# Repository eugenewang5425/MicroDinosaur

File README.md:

# MicroDinosaur

基于 Microduck 改型的小型双足恐龙机器人，使用 S288 舵机、Radxa ZERO 3W、Blender 和 Python。当前工作包括机械与打印适配、板载深度感知、IMU 接入和双总线电控设计。开发中使用 AI 辅助；来源与许可见 [NOTICE](NOTICE.md)。

**更新至 2026-11-08。默认分支只保存最新交付文件，旧版本可从 Git 提交历史查看。** 当前仍为研究原型，实机站立、行走、完整装配和制造验证尚未完成。

| 内容 | 当前入口 | 状态 |
| --- | --- | --- |
| 整机 CAD | [MicroDinosaur_Current.blend](current/MicroDinosaur_Current.blend) | OS-M02，11 月 2 日更新；150 对象、124 网格、6 条保留驱动 |
| 打印工程 | [MicroDinosaur_Print.3mf](current/MicroDinosaur_Print.3mf) | 8 盘 30 件，与当前模型配套 |
| 整机零位校准架 | [三件夹具、两盘工程与示意图](current/calibration_fixture/README.md) | 11月8日最新试装版；两盘切片通过，实物配合与承载待验 |
| 头部集成板 | [KiCad 工程与说明](hardware/head_hat/README.md) | 65×30 mm 六层；原生 DRC 0 错误、0 警告、0 未连接；未打样验收 |
| S288 主机接口 | [双总线适配代码](hardware/head_hat/software/README.md) | 帧编码、CRC、端口绑定与 EEPROM 工具；待实板联调 |
| IMU | [接线、读取程序与数据](hardware/imu/README.md) | F411 与 ZERO 3W 基础读取通过；异常跳点待排查 |
| 板载感知 | [当前源码、模型与复测边界](software/perception/README.md) | 相机/NPU 功能已恢复；散热后持续性能待复测 |

完整阶段和下一步见 [项目状态](PROJECT_STATUS.md)，机械使用边界见 [当前设计](CURRENT_DESIGN.md)。

## 获取与检查

```sh
git lfs install
git clone https://github.com/eugenewang5425/MicroDinosaur.git
cd MicroDinosaur
git lfs pull
python scripts/verify_current.py
```

CAD 和 RKNN 权重通过 Git LFS 保存。直接下载 ZIP 时，需确认大文件不是 LFS 指针。用 Blender 4.5 打开 `current/MicroDinosaur_Current.blend`，用 Bambu Studio 打开原生 `current/MicroDinosaur_Print.3mf`；先核对打印机、材料和工艺。读取或打开文件不会下发打印任务。

当前模型保留 19 个舵机参照实例，但只有 6 条现有驱动；不能据此宣称完整 19 轴运动链已经绑定。旧 v07 的质量台账、19 驱动和仿真验收不适用于当前 OS-M02。

仓库不保存中间整机、`.blend1`、前后重复副本、过程截图、失败候选、完整日志、工具安装包、个人设备配置和实时标定记录。各模块只附与本次交付有关的最终检查或测量结果。

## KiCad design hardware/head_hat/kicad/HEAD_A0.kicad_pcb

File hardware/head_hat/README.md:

# 当前头部集成板

最新候选：**B2 V3 / 2026-11-07**。65×30 mm，六层，279 个过孔、3938 段走线。KiCad 9.0.9 原生 DRC 为 0 错误、0 警告、0 未连接。当前为设计审阅候选，尚未实物打样与制造放行。

打开 [kicad/HEAD_A0.kicad_pro](kicad/HEAD_A0.kicad_pro)。工程内部文件名沿用 HEAD_A0，不代表这是早期 A0 版本；本目录只包含这一份最新候选。符号与封装库使用 `${KIPRJMOD}` 相对引用，已随工程保存。[BOM](BOM.csv) 对应保留的 B2 器件布置。

功能包括降压与电源保护、音频、板载头部 IMU、FT2232H 双 UART 与两路 S288 半双工接口，并保留身体 IMU、ToF 接口。独立串口与协议适配代码见 [software](software/README.md)。FT2232H 自带 USB/UART，不需要烧写宇树 STM32 示例。

最终 [DRC](validation/final_drc.json) 与 [几何汇总](validation/summary.json) 绑定 PCB SHA256 `566901eef7e306b5e4f0bd7f48aab18467615563099a4b934d516693c2ad7f8a`。115 个接地过孔与 71 个供电过孔保留；USB 差分对和有源 MEMS 时钟铜线保留。检测到的同层共线重复段为 0；这是局部 CAD 检查结果，不是信号完整性或实物性能结论。

本版未完成实板时钟、USB 阻抗、EMI、最大电流/温升或整机装配验证。Radxa 的 USB GPIO 引出需要核对并执行相应硬件电阻选择，当前不是即插即用连接。S288 整串动力仍需电池分组注电，PH 接口和支路保险不等于整腿堵转电流承载能力。本包不提供旧 B2 的 Gerber，避免与当前走线混用；投板前须以本版原生工程完成电气与制造复核。

来源与许可见 [NOTICE](NOTICE.md) 和 [LICENSE](LICENSE)。

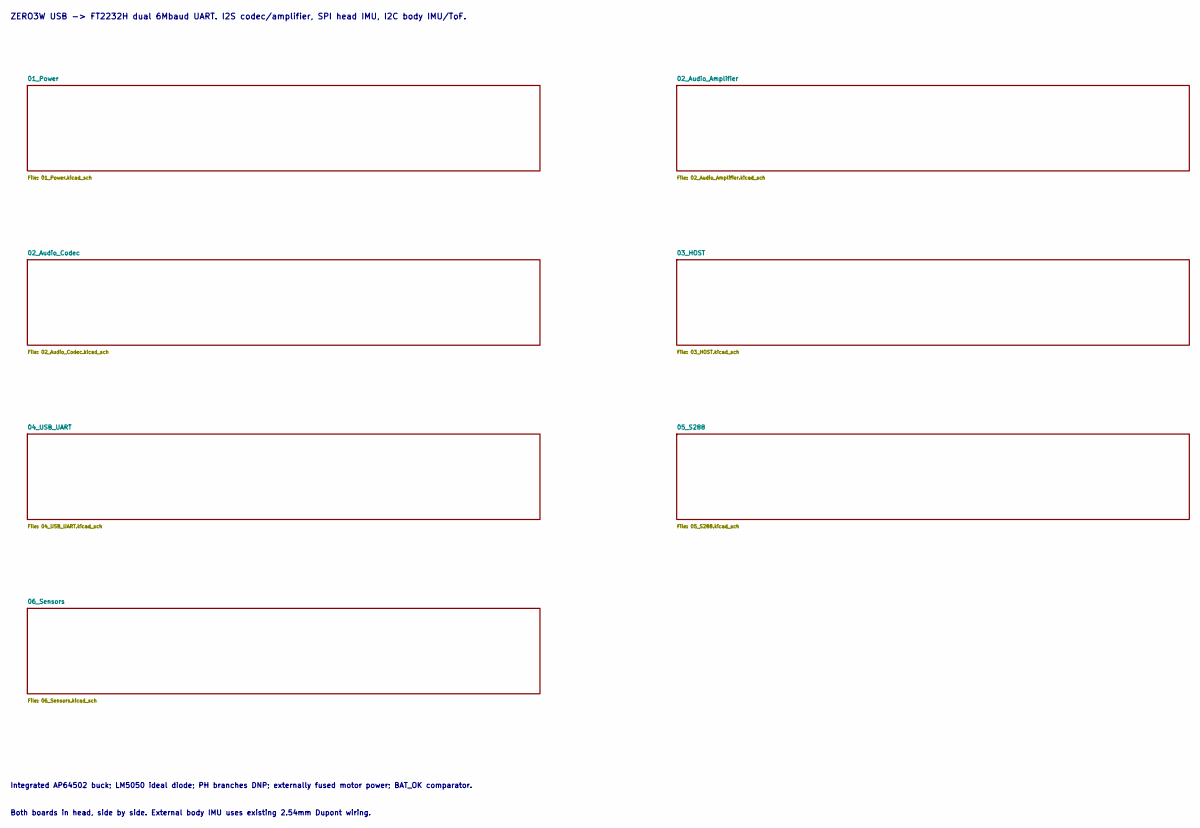
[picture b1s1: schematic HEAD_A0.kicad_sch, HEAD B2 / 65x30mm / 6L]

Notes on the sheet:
ZERO3W USB -> FT2232H dual 6Mbaud UART. I2S codec/amplifier, SPI head IMU, I2C body IMU/ToF.
Integrated AP64502 buck; LM5050 ideal diode; PH branches DNP; externally fused motor power; BAT_OK comparator.
Both boards in head, side by side. External body IMU uses existing 2.54mm Dupont wiring.

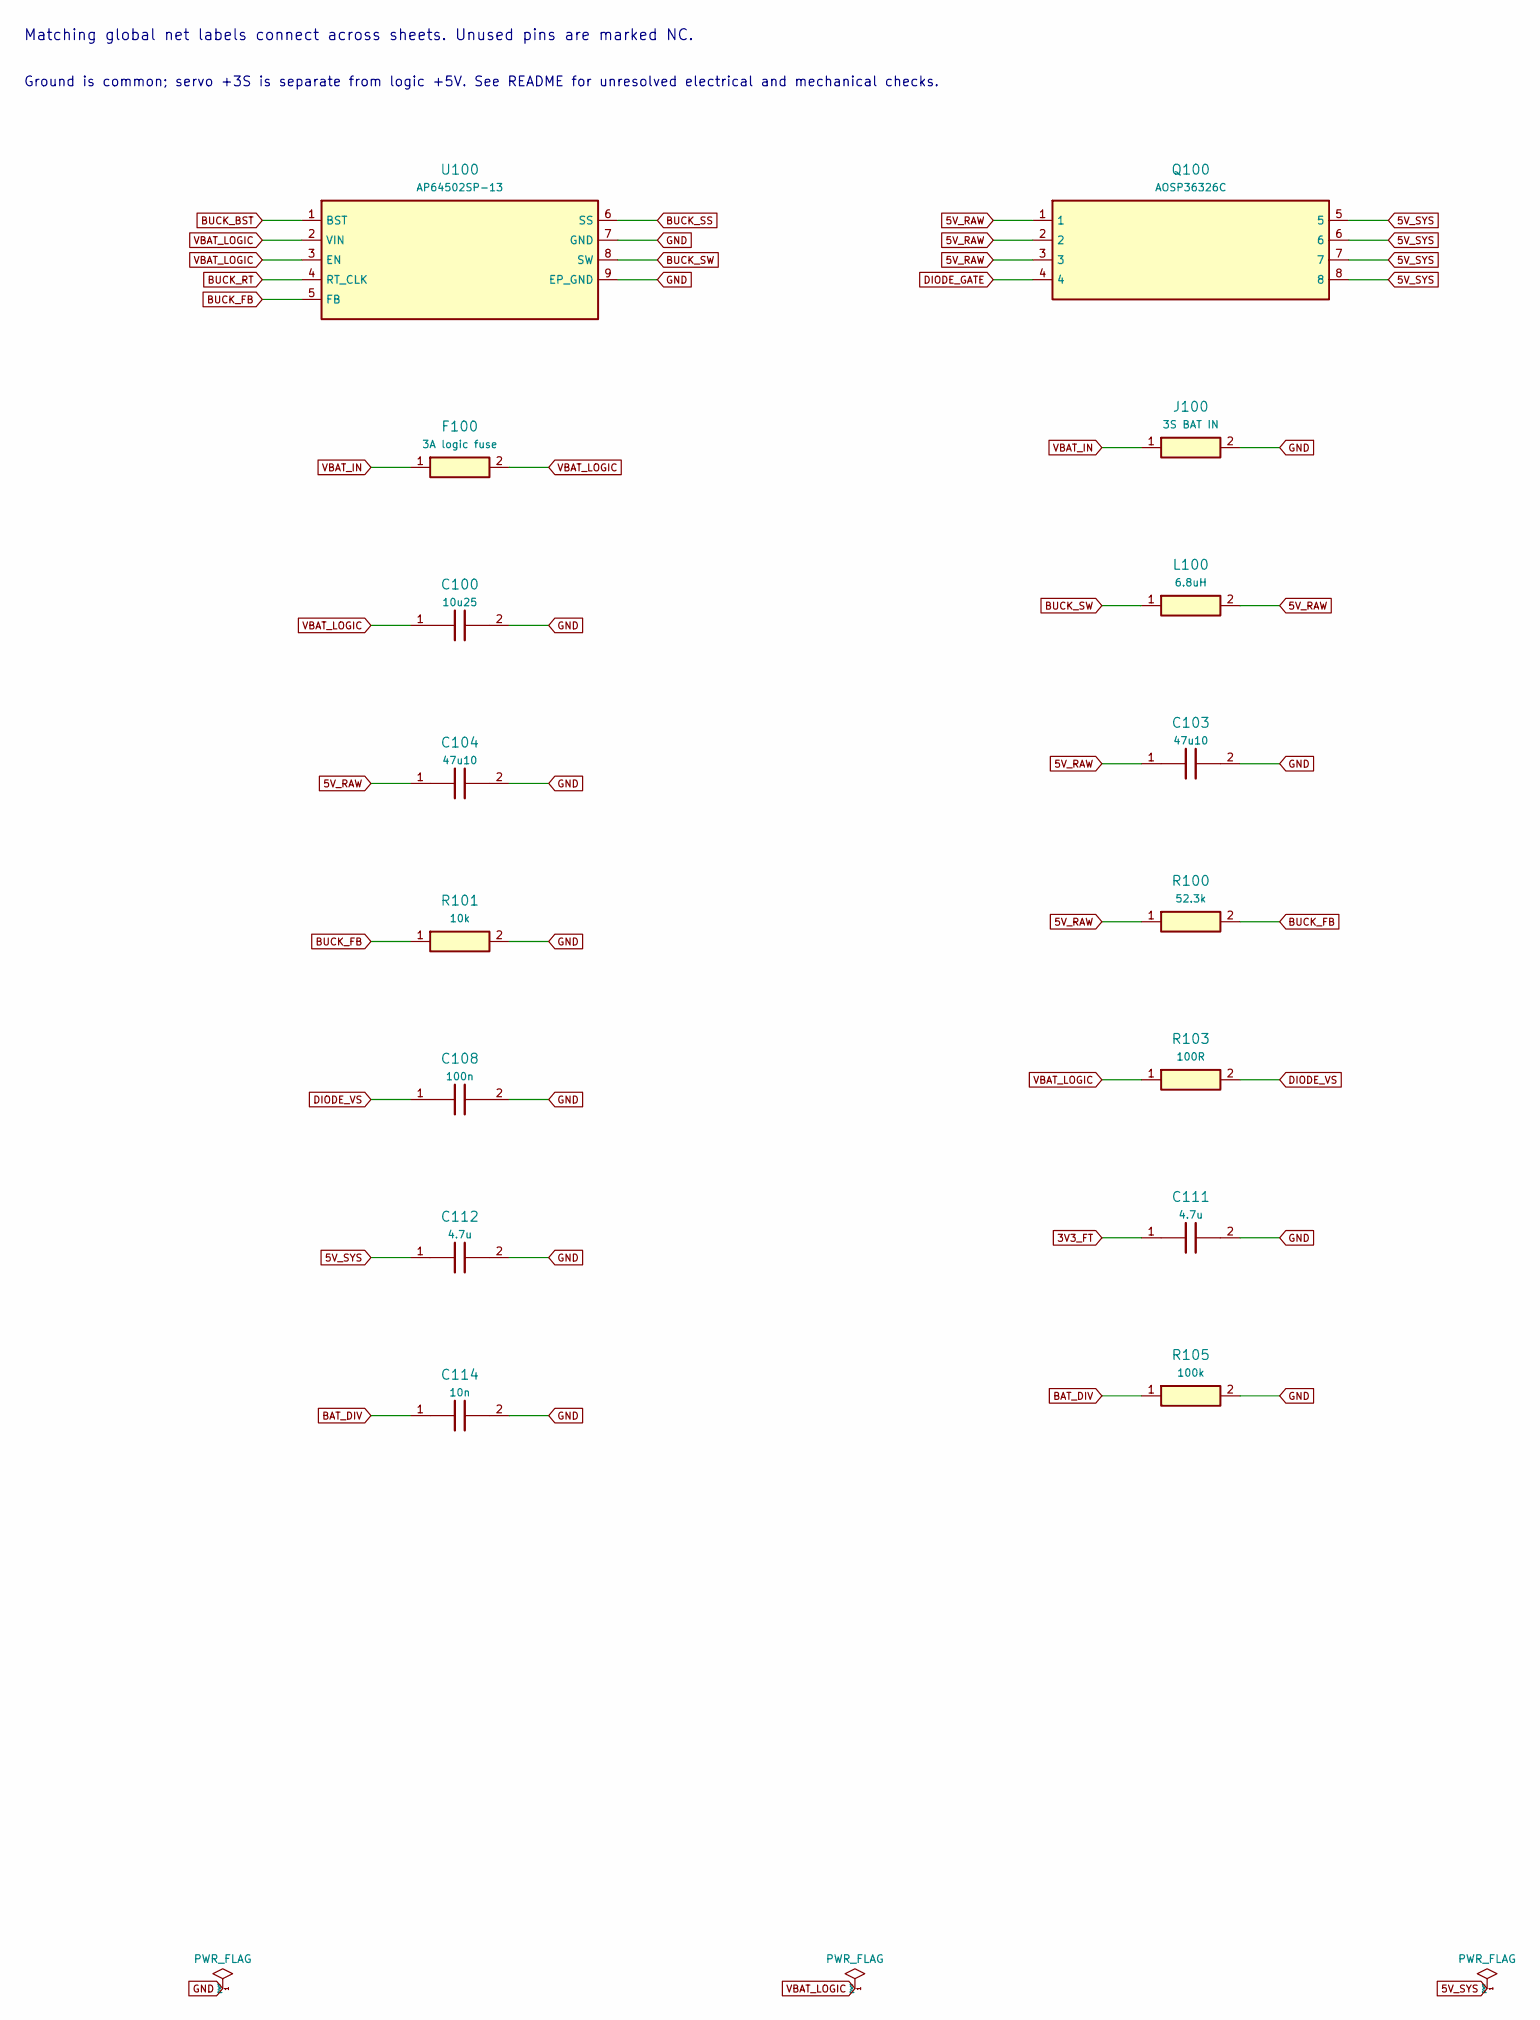
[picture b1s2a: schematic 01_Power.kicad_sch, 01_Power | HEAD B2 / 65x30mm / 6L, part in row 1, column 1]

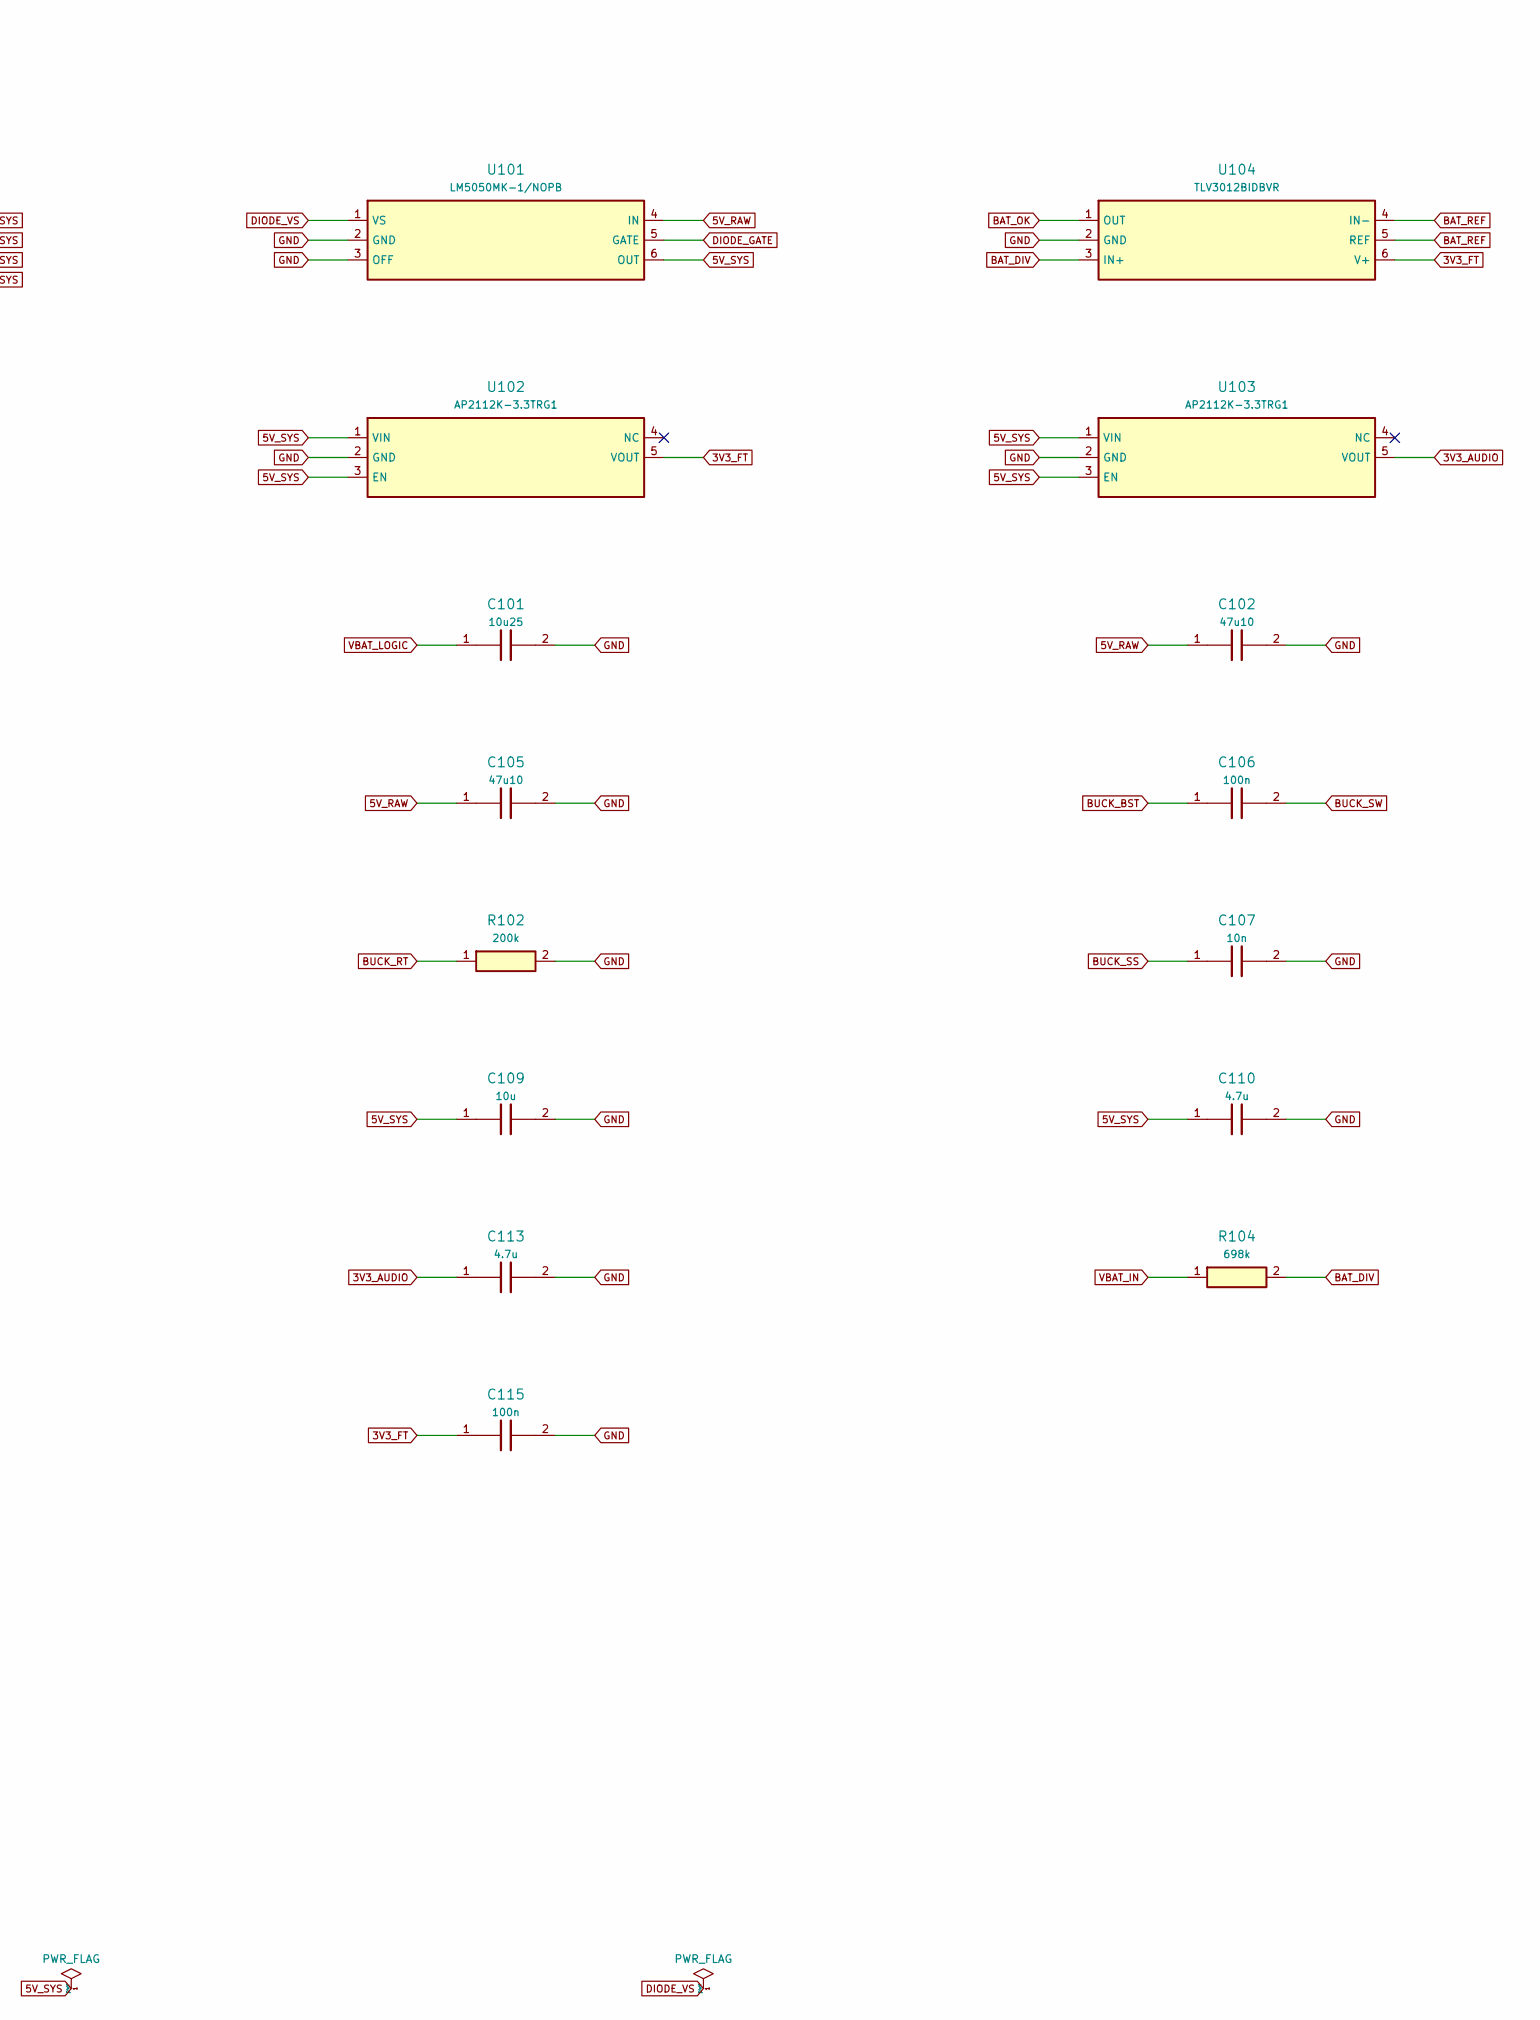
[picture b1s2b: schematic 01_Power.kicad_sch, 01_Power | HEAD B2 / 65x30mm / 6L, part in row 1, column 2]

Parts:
C100, C101: 10u25; Capacitor_SMD__C_1206_3216Metric; MPN GRM31CR71E106KA12L
C102, C103, C104, C105: 47u10; Capacitor_SMD__C_1210_3225Metric; MPN GRM32ER71A476KE15L
C106, C115: 100n; Capacitor_SMD__C_0402_1005Metric; MPN GRM155R71C104KA88D
C107, C114: 10n; Capacitor_SMD__C_0402_1005Metric; MPN GRM155R71H103KA88D
C108: 100n; Capacitor_SMD__C_0402_1005Metric; MPN GRM155R71H104KE14D
C109: 10u; Capacitor_SMD__C_0603_1608Metric; MPN GRM188R61A106KE69D
C110, C111, C112, C113: 4.7u; Capacitor_SMD__C_0603_1608Metric; MPN GRM188R60J475KE19D
F100: 3A logic fuse; Fuse__Fuse_1206_3216Metric; MPN 0467003.NR
J100: 3S BAT IN; Connector_Molex__Molex_Nano-Fit_105313-xx02_1x02_P2.50mm_Ho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; MPN 1053131202
L100: 6.8uH; Inductor_SMD__L_Coilcraft_XAL6060-XXX; MPN XAL6060-682MEC
Q100: AOSP36326C; Package_SO__SOIC-8_3.9x4.9mm_P1.27mm; MPN AOSP36326C
R100: 52.3k; Resistor_SMD__R_0402_1005Metric; MPN RC0402FR-0752K3L
R101: 10k; Resistor_SMD__R_0402_1005Metric; MPN RC0402FR-0710KL
R102: 200k; Resistor_SMD__R_0402_1005Metric; MPN RC0402FR-07200KL
R103: 100R; Resistor_SMD__R_0402_1005Metric; MPN RC0402FR-07100RL
R104: 698k; Resistor_SMD__R_0402_1005Metric; MPN RC0402FR-07698KL
R105: 100k; Resistor_SMD__R_0402_1005Metric; MPN RC0402FR-07100KL
U100: AP64502SP-13; AP64502_SO8EP; MPN AP64502SP-13
U101: LM5050MK-1/NOPB; Package_TO_SOT_SMD__SOT-23-6; MPN LM5050MK-1/NOPB
U102, U103: AP2112K-3.3TRG1; Package_TO_SOT_SMD__SOT-23-5; MPN AP2112K-3.3TRG1
U104: TLV3012BIDBVR; Package_TO_SOT_SMD__SOT-23-6; MPN TLV3012BIDBVR

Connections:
3V3_AUDIO: C113.1, U103.5 (VOUT); also elsewhere on the board
3V3_FT: C111.1, C115.1, U102.5 (VOUT), U104.6 (V+); also elsewhere on the board
5V_RAW: C102.1, C103.1, C104.1, C105.1, L100.2, Q100.1, Q100.2, Q100.3, R100.1, U101.4 (IN)
5V_SYS: C109.1, C110.1, C112.1, Q100.5, Q100.6, Q100.7, Q100.8, U101.6 (OUT), U102.1 (VIN), U102.3 (EN), U103.1 (VIN), U103.3 (EN); also elsewhere on the board
BAT_DIV: C114.1, R104.2, R105.1, U104.3 (IN+)
BAT_OK: U104.1 (OUT); also elsewhere on the board
BAT_REF: U104.4 (IN-), U104.5 (REF)
BUCK_BST: C106.1, U100.1 (BST)
BUCK_FB: R100.2, R101.1, U100.5 (FB)
BUCK_RT: R102.1, U100.4 (RT_CLK)
BUCK_SS: C107.1, U100.6 (SS)
BUCK_SW: C106.2, L100.1, U100.8 (SW)
DIODE_GATE: Q100.4, U101.5 (GATE)
DIODE_VS: C108.1, R103.2, U101.1 (VS)
GND: C100.2, C101.2, C102.2, C103.2, C104.2, C105.2, C107.2, C108.2, C109.2, C110.2, C111.2, C112.2, C113.2, C114.2, C115.2, J100.2, R101.2, R102.2, R105.2, U100.7 (GND), U100.9 (EP_GND), U101.2 (GND), U101.3 (OFF), U102.2 (GND), U103.2 (GND), U104.2 (GND); also elsewhere on the board
VBAT_IN: F100.1, J100.1, R104.1; also elsewhere on the board
VBAT_LOGIC: C100.1, C101.1, F100.2, R103.1, U100.2 (VIN), U100.3 (EN)

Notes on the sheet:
Matching global net labels connect across sheets. Unused pins are marked NC.
Ground is common; servo +3S is separate from logic +5V. See README for unresolved electrical and mechanical checks.

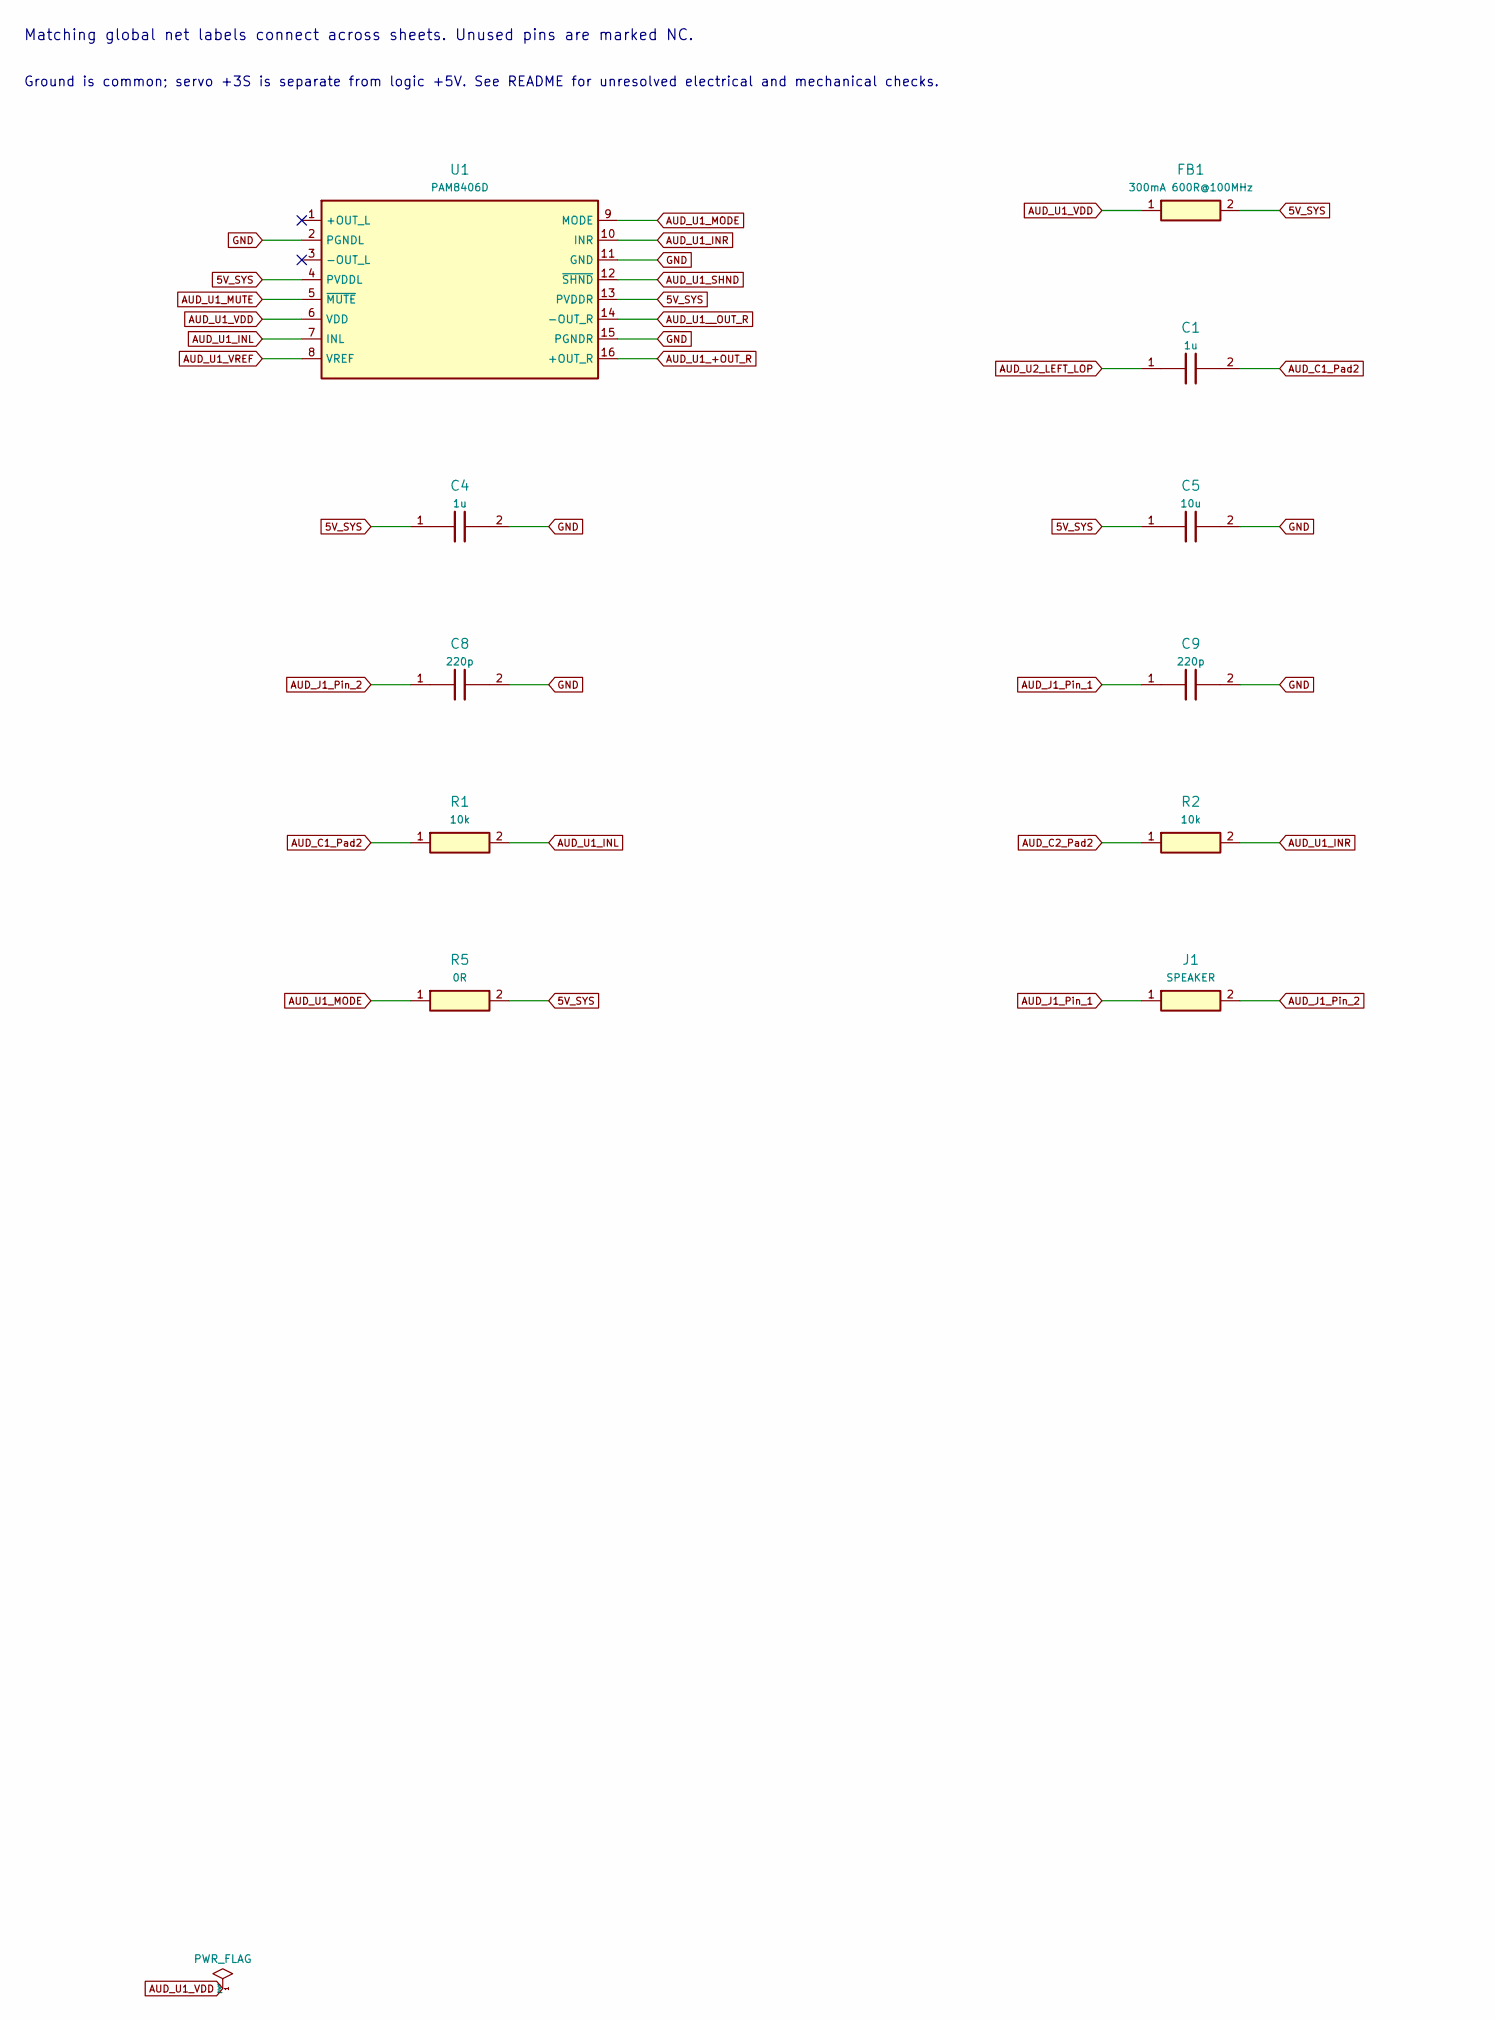
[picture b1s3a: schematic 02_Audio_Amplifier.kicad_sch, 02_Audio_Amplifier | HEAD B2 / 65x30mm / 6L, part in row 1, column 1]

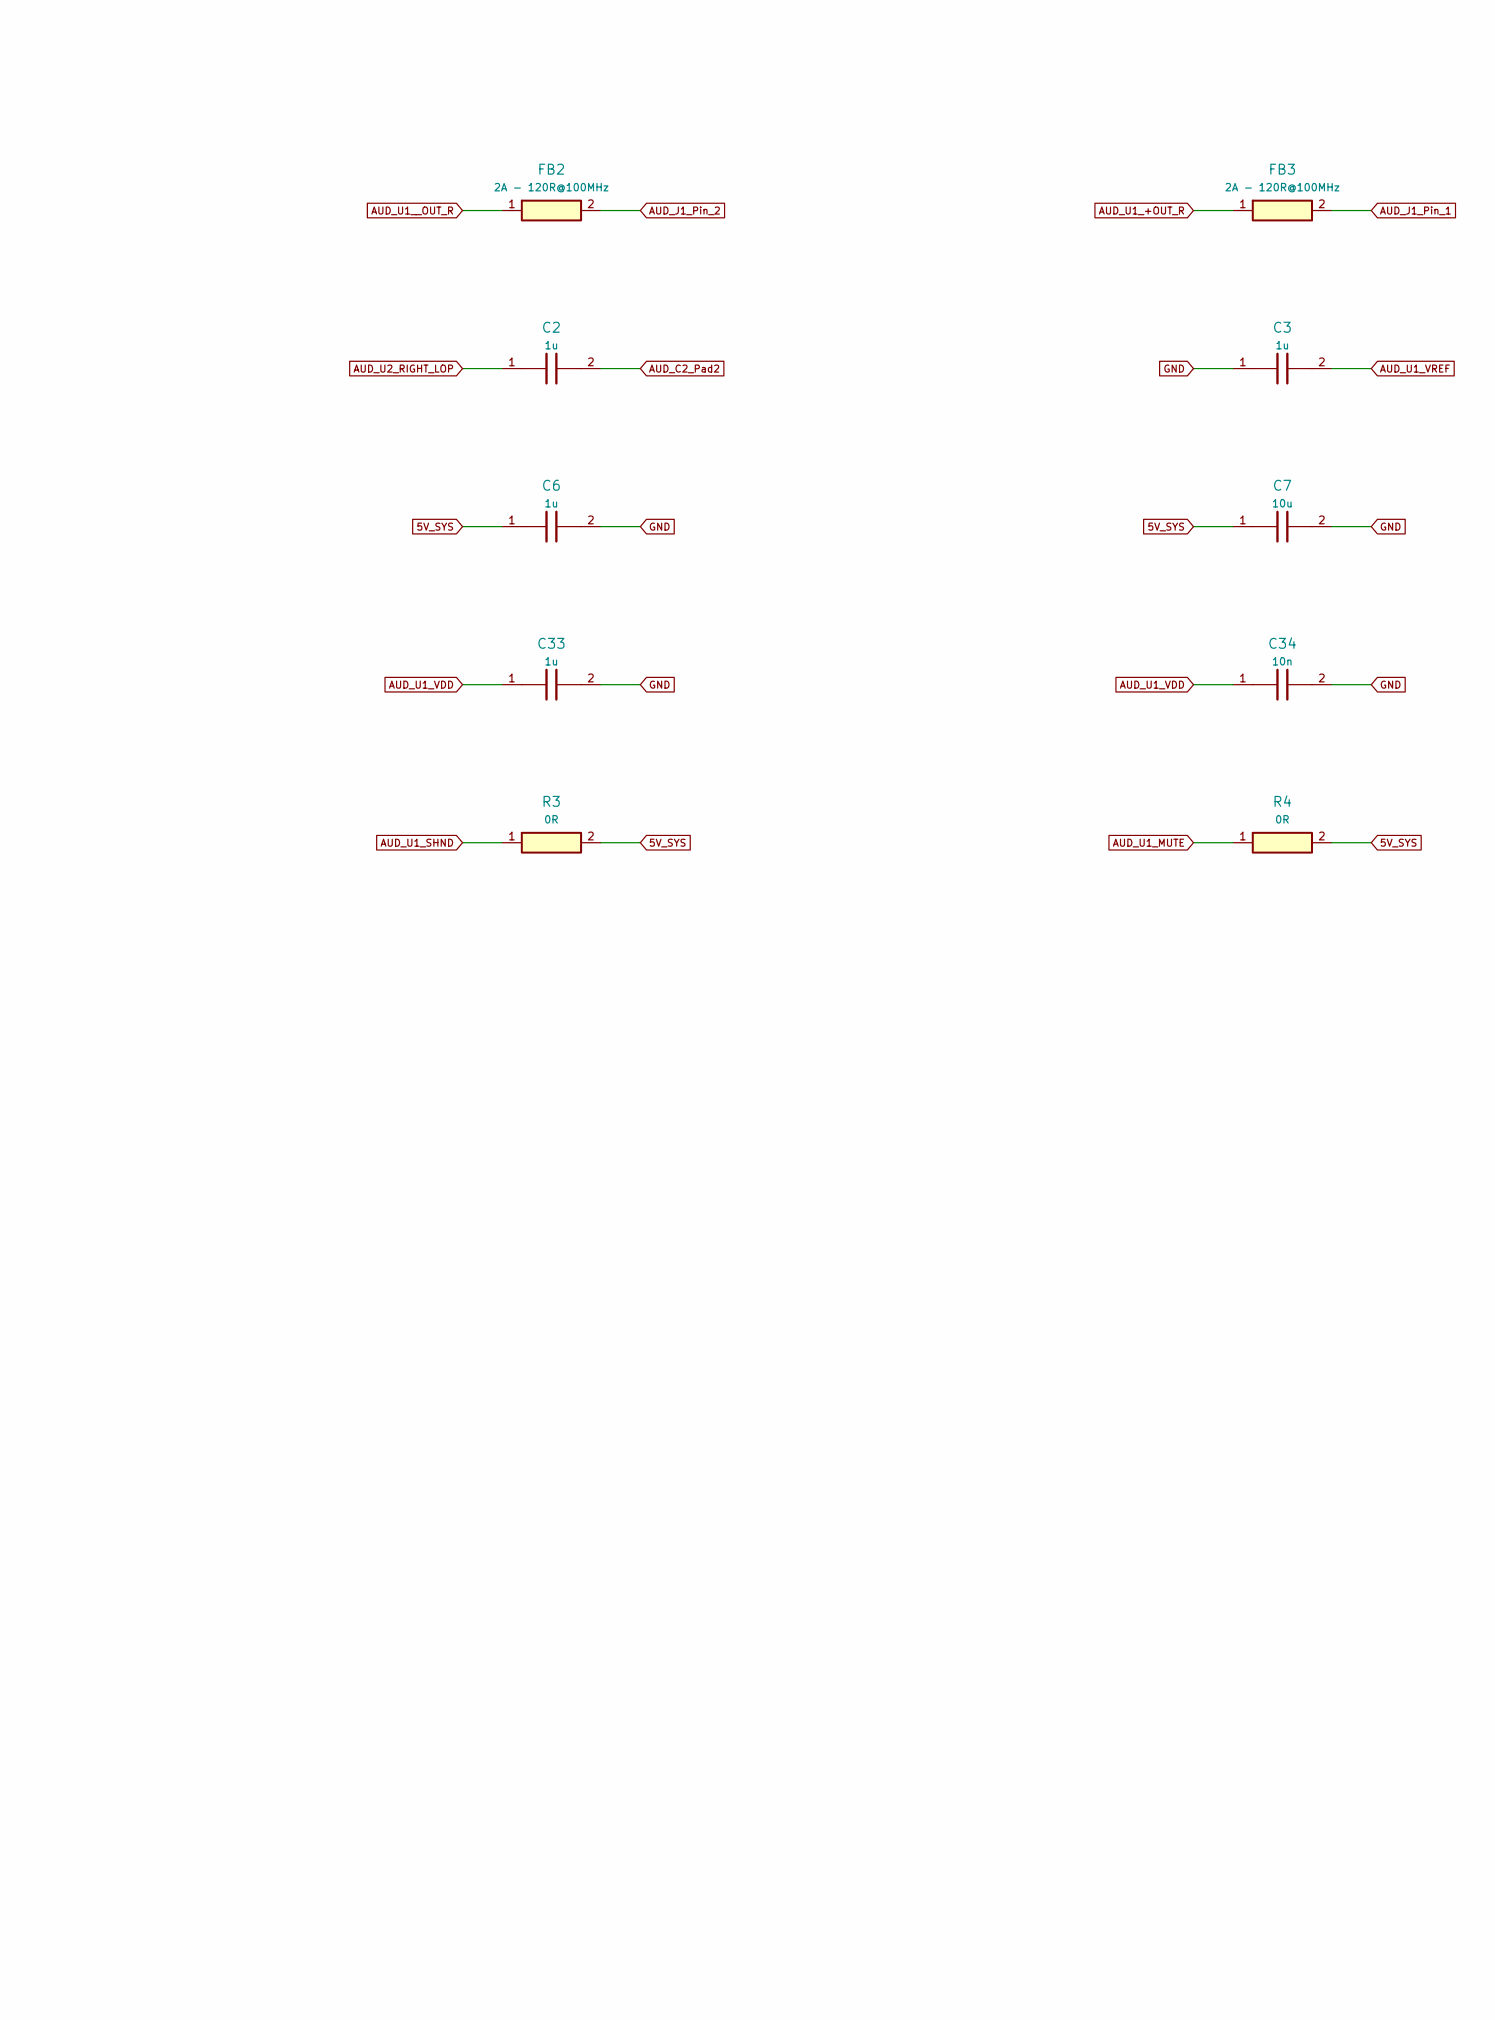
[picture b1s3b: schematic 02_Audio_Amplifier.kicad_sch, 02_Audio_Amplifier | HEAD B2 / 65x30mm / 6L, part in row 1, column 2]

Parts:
C1, C2, C3, C4, C6, C33: 1u; Capacitor_SMD__C_0402_1005Metric; MPN GRM155R61A105KE15D
C5, C7: 10u; Capacitor_SMD__C_0603_1608Metric; MPN GRM188R61A106KE69D
C8, C9: 220p; Capacitor_SMD__C_0603_1608Metric; MPN GRM1885C1H221JA01D
C34: 10n; Capacitor_SMD__C_0402_1005Metric; MPN GRM155R71H103KA88D
FB1: 300mA 600R@100MHz; Pollen_FB1; MPN BLM15AG601SN1D
FB2: 2A - 120R@100MHz; Pollen_FB2; MPN BLM15PX121SN1D
FB3: 2A - 120R@100MHz; Pollen_FB3; MPN BLM15PX121SN1D
J1: SPEAKER; Connector_JST__JST_PH_B2B-PH-K_1x02_P2.00mm_Vertical; MPN B2B-PH-K-S
R1, R2: 10k; Resistor_SMD__R_0402_1005Metric; MPN RC0402FR-0710KL
R3, R4, R5: 0R; Resistor_SMD__R_0402_1005Metric; MPN RC0402JR-070RL
U1: PAM8406D; Pollen_U1; MPN PAM8406DR

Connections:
5V_SYS: C4.1, C5.1, C6.1, C7.1, FB1.2, R3.2, R4.2, R5.2, U1.4 (PVDDL), U1.13 (PVDDR); also elsewhere on the board
AUD_C1_Pad2: C1.2, R1.1
AUD_C2_Pad2: C2.2, R2.1
AUD_J1_Pin_1: C9.1, FB3.2, J1.1
AUD_J1_Pin_2: C8.1, FB2.2, J1.2
AUD_U1_+OUT_R: FB3.1, U1.16 (+OUT_R)
AUD_U1_INL: R1.2, U1.7 (INL)
AUD_U1_INR: R2.2, U1.10 (INR)
AUD_U1_MODE: R5.1, U1.9 (MODE)
AUD_U1_MUTE: R4.1, U1.5 (~MUTE)
AUD_U1_SHND: R3.1, U1.12 (~SHND)
AUD_U1_VDD: C33.1, C34.1, FB1.1, U1.6 (VDD)
AUD_U1_VREF: C3.2, U1.8 (VREF)
AUD_U1__OUT_R: FB2.1, U1.14 (-OUT_R)
AUD_U2_LEFT_LOP: C1.1; also elsewhere on the board
AUD_U2_RIGHT_LOP: C2.1; also elsewhere on the board
GND: C3.1, C4.2, C5.2, C6.2, C7.2, C8.2, C9.2, C33.2, C34.2, U1.2 (PGNDL), U1.11 (GND), U1.15 (PGNDR); also elsewhere on the board

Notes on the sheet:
Matching global net labels connect across sheets. Unused pins are marked NC.
Ground is common; servo +3S is separate from logic +5V. See README for unresolved electrical and mechanical checks.

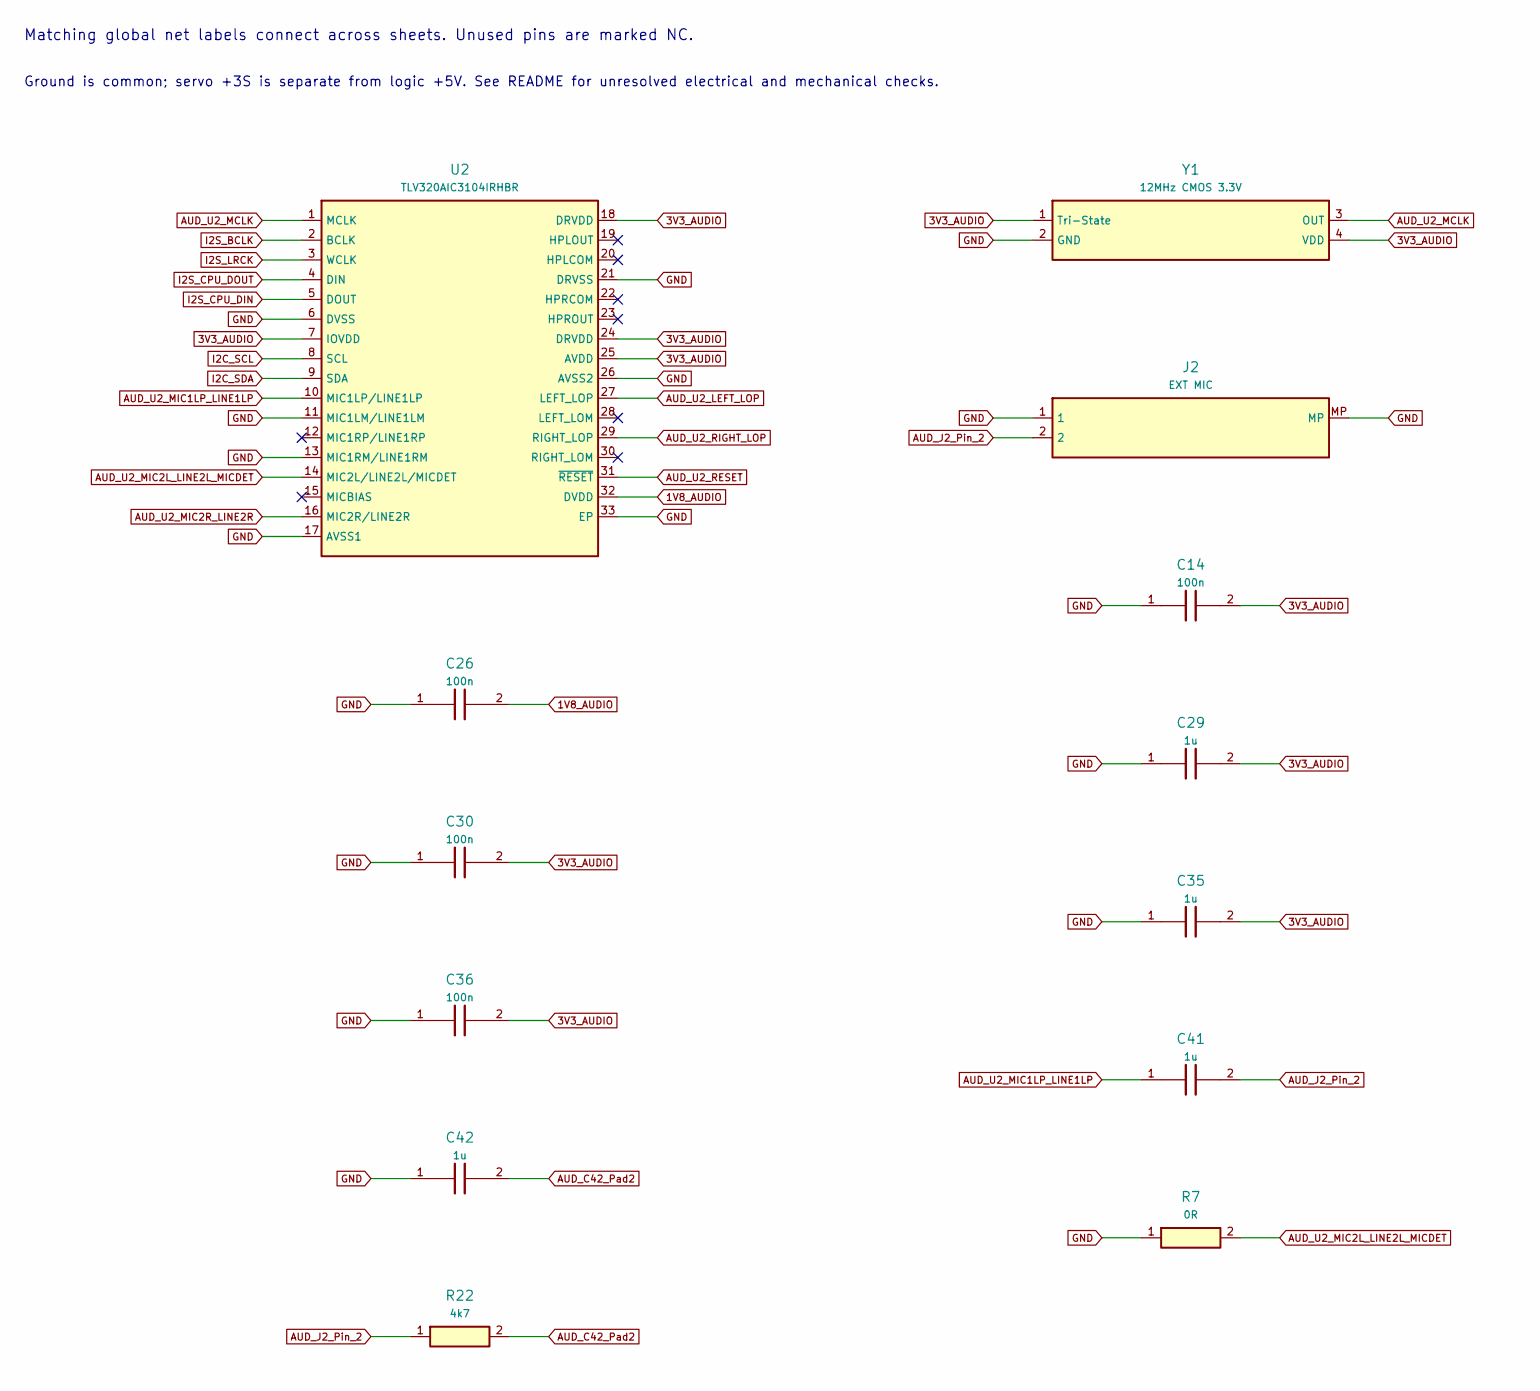
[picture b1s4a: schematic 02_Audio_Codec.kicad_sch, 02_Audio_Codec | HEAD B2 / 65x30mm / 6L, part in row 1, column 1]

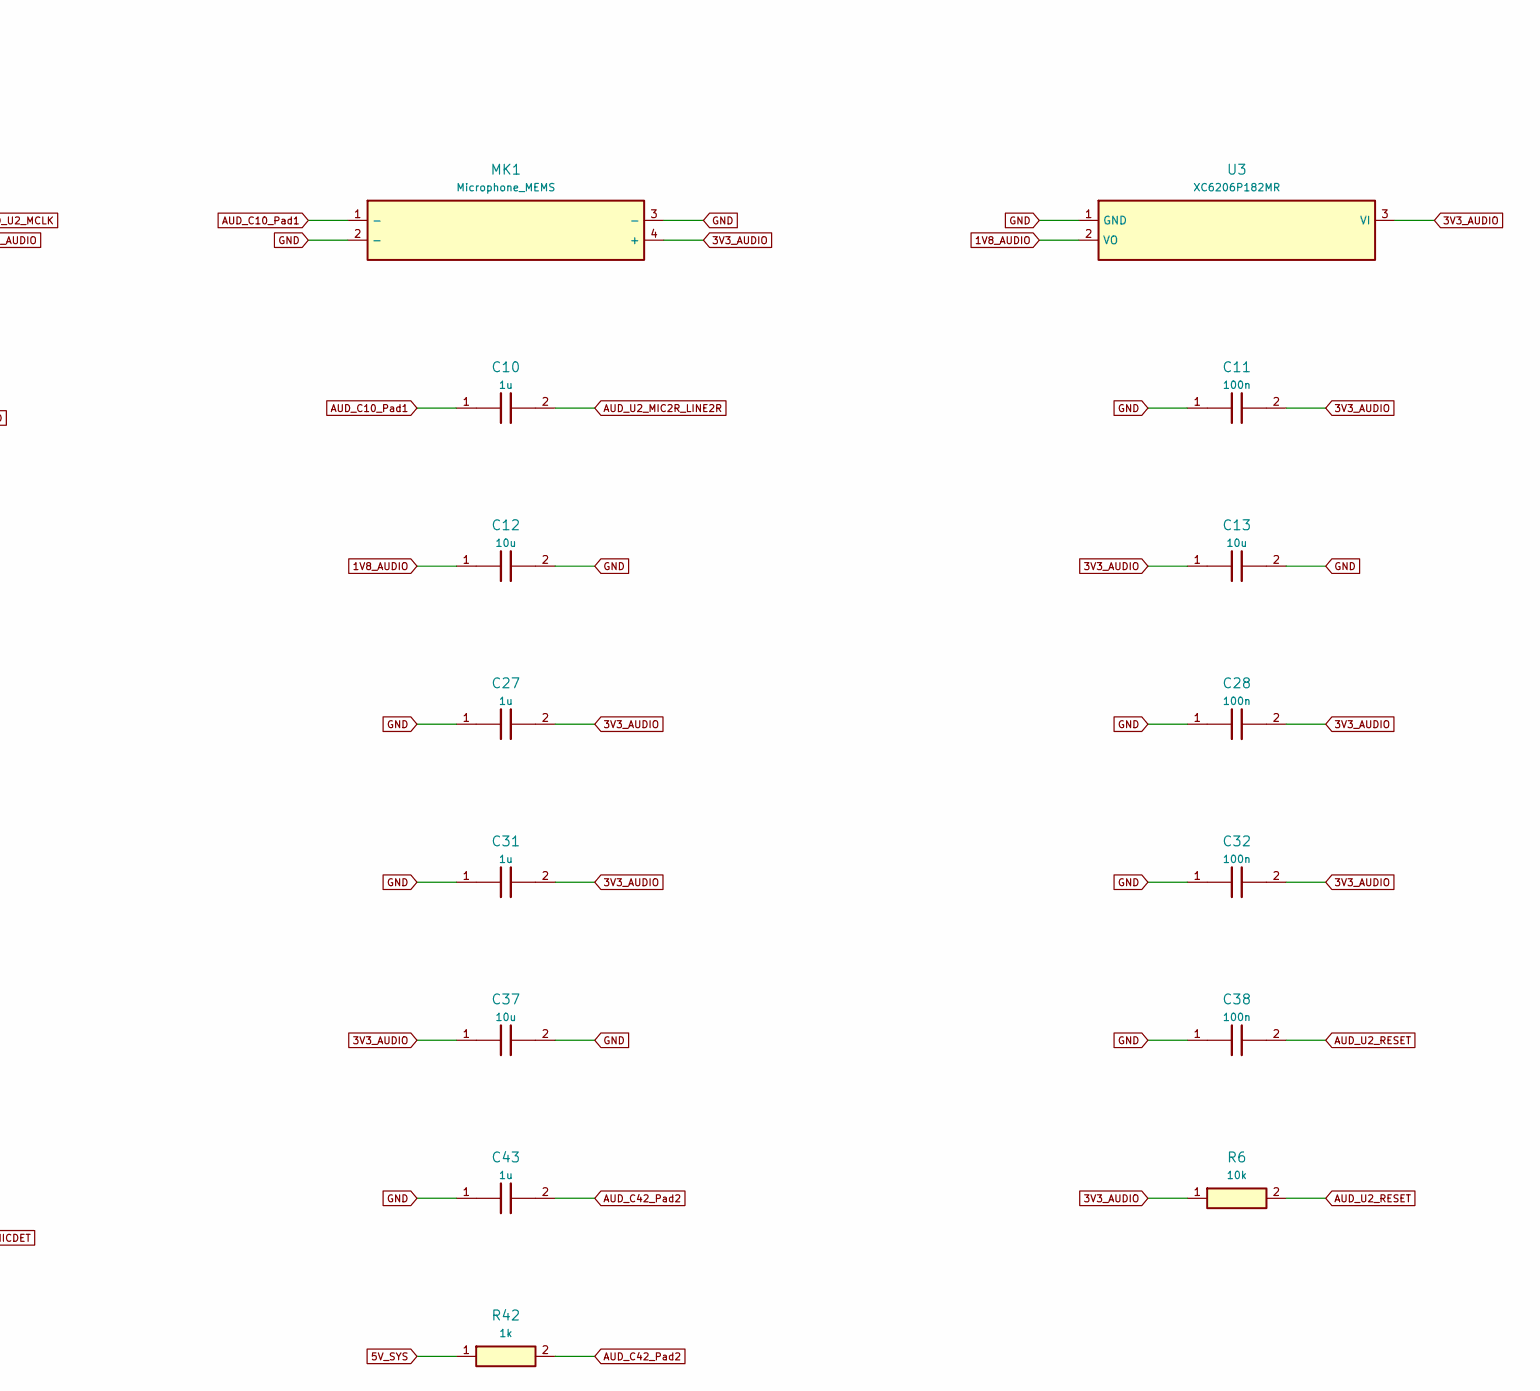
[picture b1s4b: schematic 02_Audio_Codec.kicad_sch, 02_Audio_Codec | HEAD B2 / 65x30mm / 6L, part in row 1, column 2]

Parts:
C10, C27, C29, C31, C35, C41, C42, C43: 1u; Capacitor_SMD__C_0402_1005Metric; MPN GRM155R61A105KE15D
C11, C14, C26, C28, C30, C32, C36, C38: 100n; Capacitor_SMD__C_0402_1005Metric; MPN GRM155R71C104KA88D
C12, C13, C37: 10u; Capacitor_SMD__C_0603_1608Metric; MPN GRM188R61A106KE69D
J2: EXT MIC; Connector_JST__JST_SH_BM02B-SRSS-TB_1x02-1MP_P1.00mm_Vertic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; MPN BM02B-SRSS-TB(LF)(SN)
MK1: Microphone_MEMS; Pollen_MK1; MPN LMA2718T421-OA5-2
R6: 10k; Resistor_SMD__R_0402_1005Metric; MPN RC0402FR-0710KL
R7: 0R; Resistor_SMD__R_0402_1005Metric; MPN RC0402JR-070RL
R22: 4k7; Resistor_SMD__R_0402_1005Metric; MPN RC0402FR-074K7L
R42: 1k; Resistor_SMD__R_0402_1005Metric; MPN RC0402FR-071KL
U2: TLV320AIC3104IRHBR; Pollen_U2; MPN TLV320AIC3104IRHBR
U3: XC6206P182MR; Pollen_U3; MPN XC6206P182MR-G
Y1: 12MHz CMOS 3.3V; Pollen_Y1; MPN ASDMB-12.000MHZ-LC-T

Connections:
1V8_AUDIO: C12.1, C26.2, U2.32 (DVDD), U3.2 (VO)
3V3_AUDIO: C11.2, C13.1, C14.2, C27.2, C28.2, C29.2, C30.2, C31.2, C32.2, C35.2, C36.2, C37.1, MK1.4 (+), R6.1, U2.7 (IOVDD), U2.18 (DRVDD), U2.24 (DRVDD), U2.25 (AVDD), U3.3 (VI), Y1.1 (Tri-State), Y1.4 (VDD); also elsewhere on the board
5V_SYS: R42.1; also elsewhere on the board
AUD_C10_Pad1: C10.1, MK1.1 (-)
AUD_C42_Pad2: C42.2, C43.2, R22.2, R42.2
AUD_J2_Pin_2: C41.2, J2.2, R22.1
AUD_U2_LEFT_LOP: U2.27 (LEFT_LOP); also elsewhere on the board
AUD_U2_MCLK: U2.1 (MCLK), Y1.3 (OUT)
AUD_U2_MIC1LP_LINE1LP: C41.1, U2.10 (MIC1LP/LINE1LP)
AUD_U2_MIC2L_LINE2L_MICDET: R7.2, U2.14 (MIC2L/LINE2L/MICDET)
AUD_U2_MIC2R_LINE2R: C10.2, U2.16 (MIC2R/LINE2R)
AUD_U2_RESET: C38.2, R6.2, U2.31 (~RESET)
AUD_U2_RIGHT_LOP: U2.29 (RIGHT_LOP); also elsewhere on the board
GND: C11.1, C12.2, C13.2, C14.1, C26.1, C27.1, C28.1, C29.1, C30.1, C31.1, C32.1, C35.1, C36.1, C37.2, C38.1, C42.1, C43.1, J2.1, J2.MP, MK1.2 (-), MK1.3 (-), R7.1, U2.6 (DVSS), U2.11 (MIC1LM/LINE1LM), U2.13 (MIC1RM/LINE1RM), U2.17 (AVSS1), U2.21 (DRVSS), U2.26 (AVSS2), U2.33 (EP), U3.1 (GND), Y1.2 (GND); also elsewhere on the board
I2C_SCL: U2.8 (SCL); also elsewhere on the board
I2C_SDA: U2.9 (SDA); also elsewhere on the board
I2S_BCLK: U2.2 (BCLK); also elsewhere on the board
I2S_CPU_DIN: U2.5 (DOUT); also elsewhere on the board
I2S_CPU_DOUT: U2.4 (DIN); also elsewhere on the board
I2S_LRCK: U2.3 (WCLK); also elsewhere on the board

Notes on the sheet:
Matching global net labels connect across sheets. Unused pins are marked NC.
Ground is common; servo +3S is separate from logic +5V. See README for unresolved electrical and mechanical checks.
